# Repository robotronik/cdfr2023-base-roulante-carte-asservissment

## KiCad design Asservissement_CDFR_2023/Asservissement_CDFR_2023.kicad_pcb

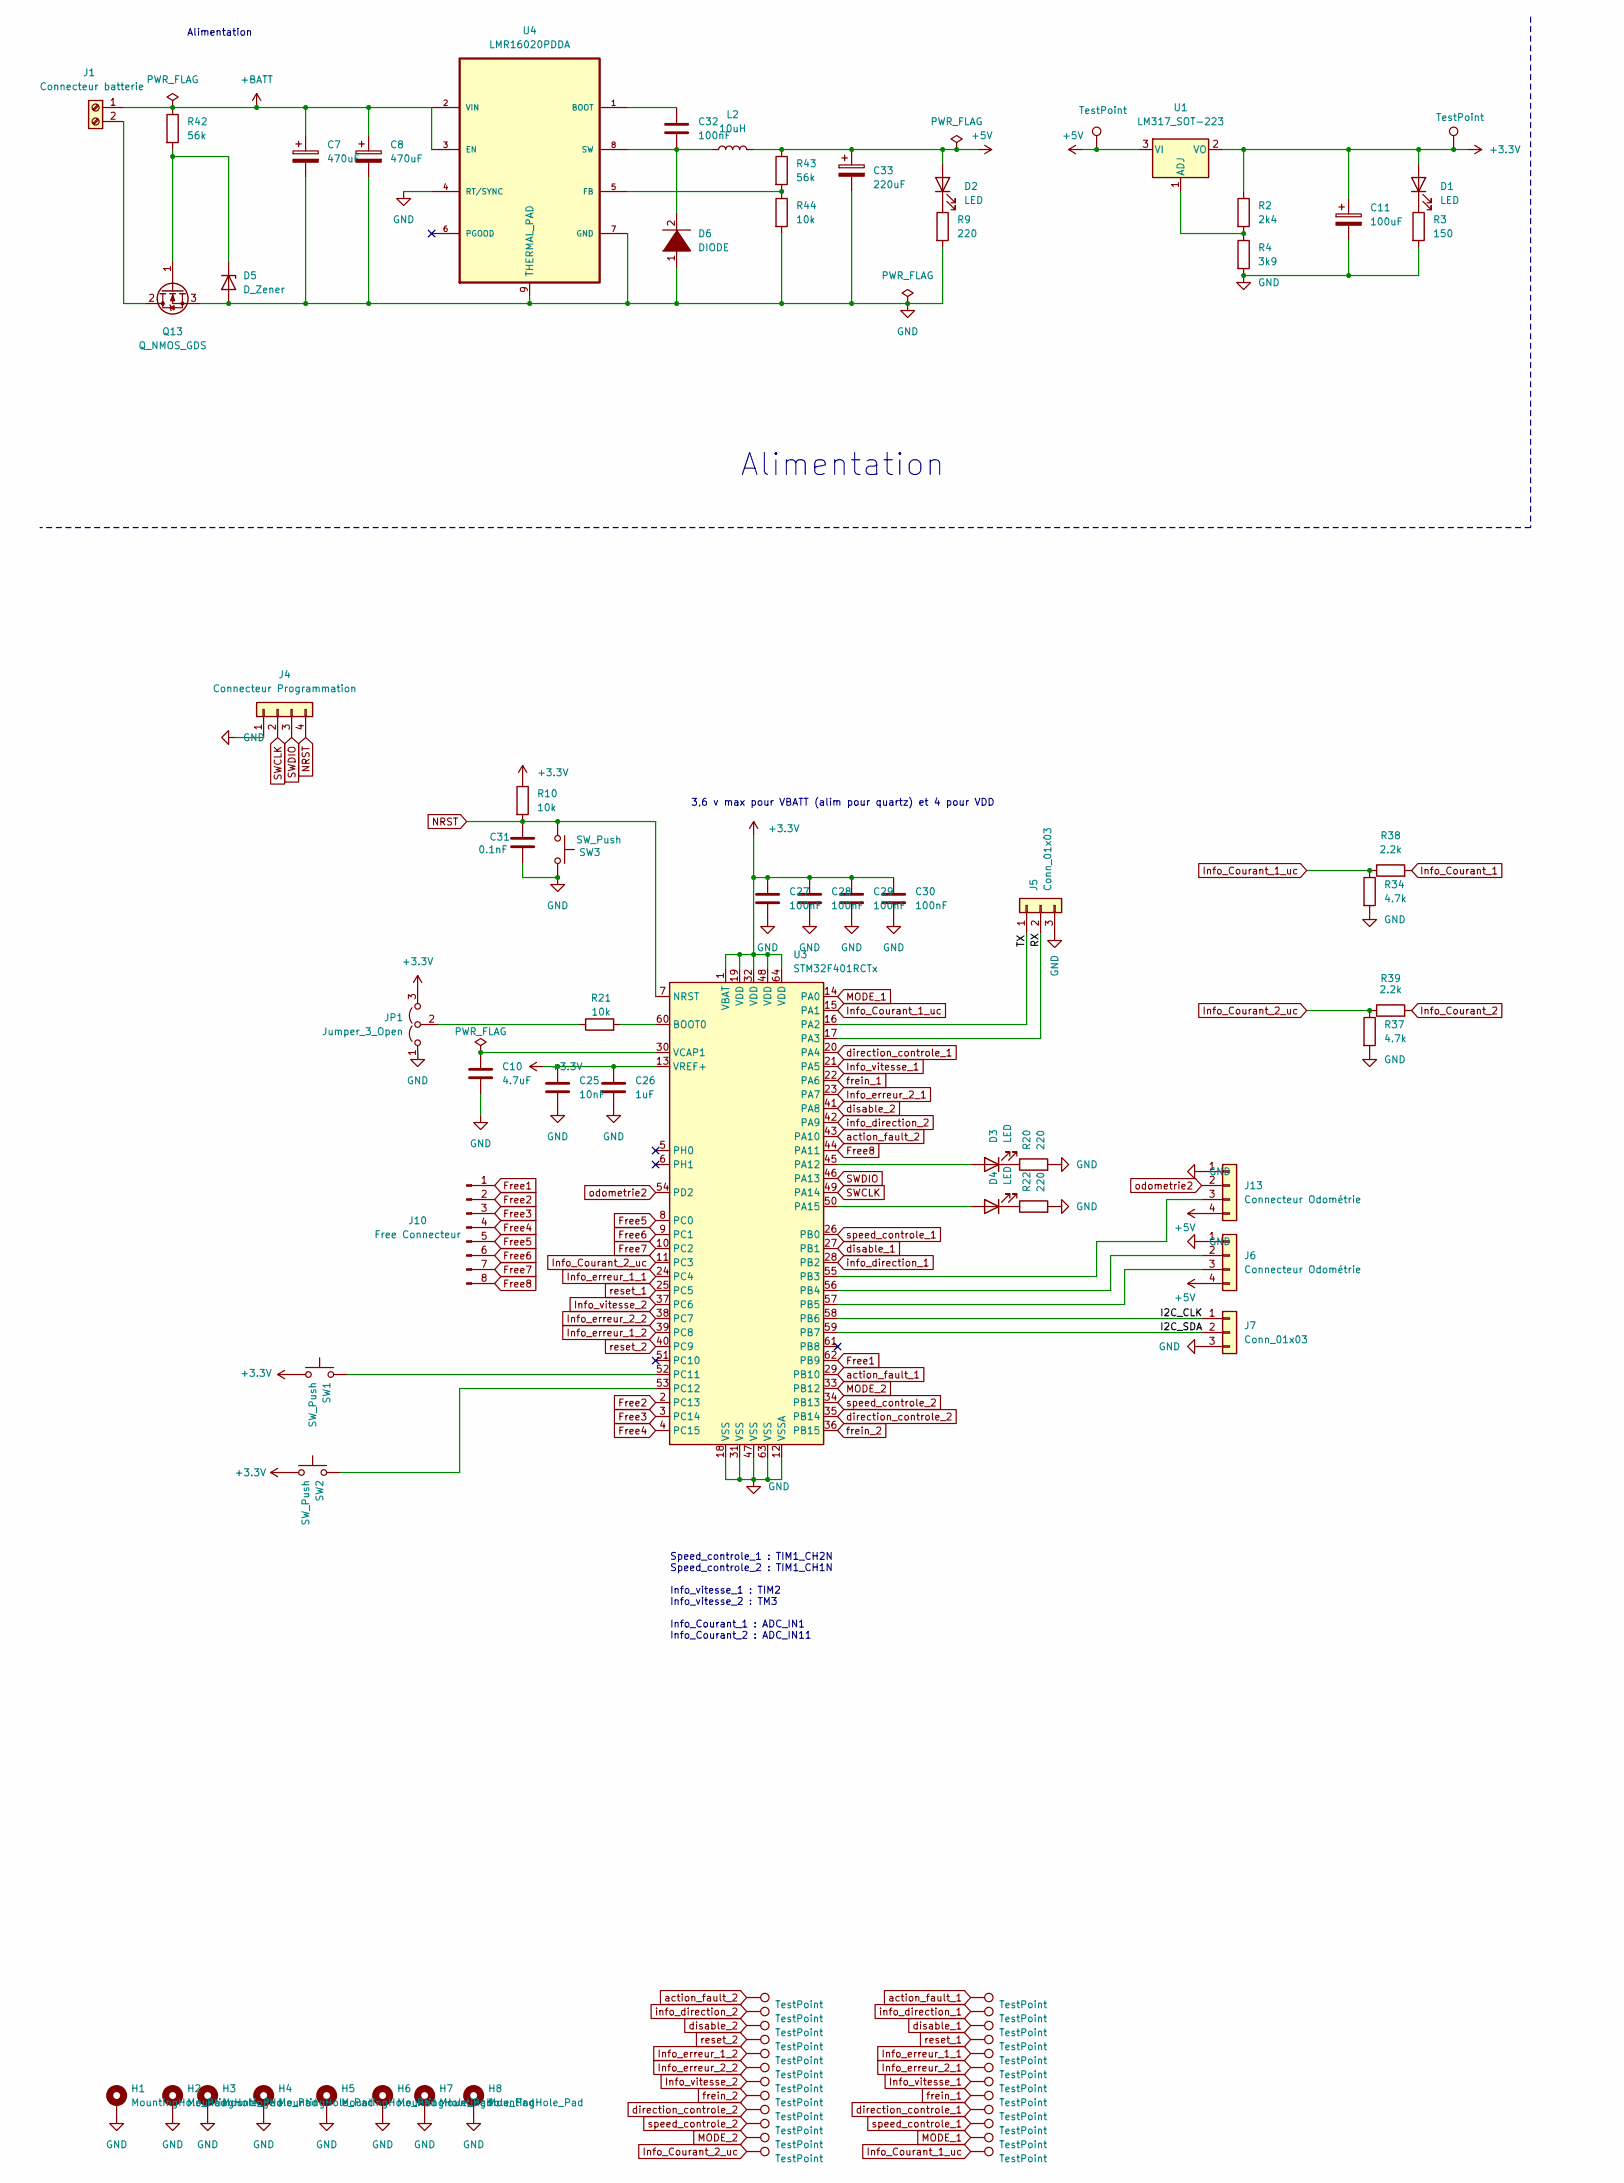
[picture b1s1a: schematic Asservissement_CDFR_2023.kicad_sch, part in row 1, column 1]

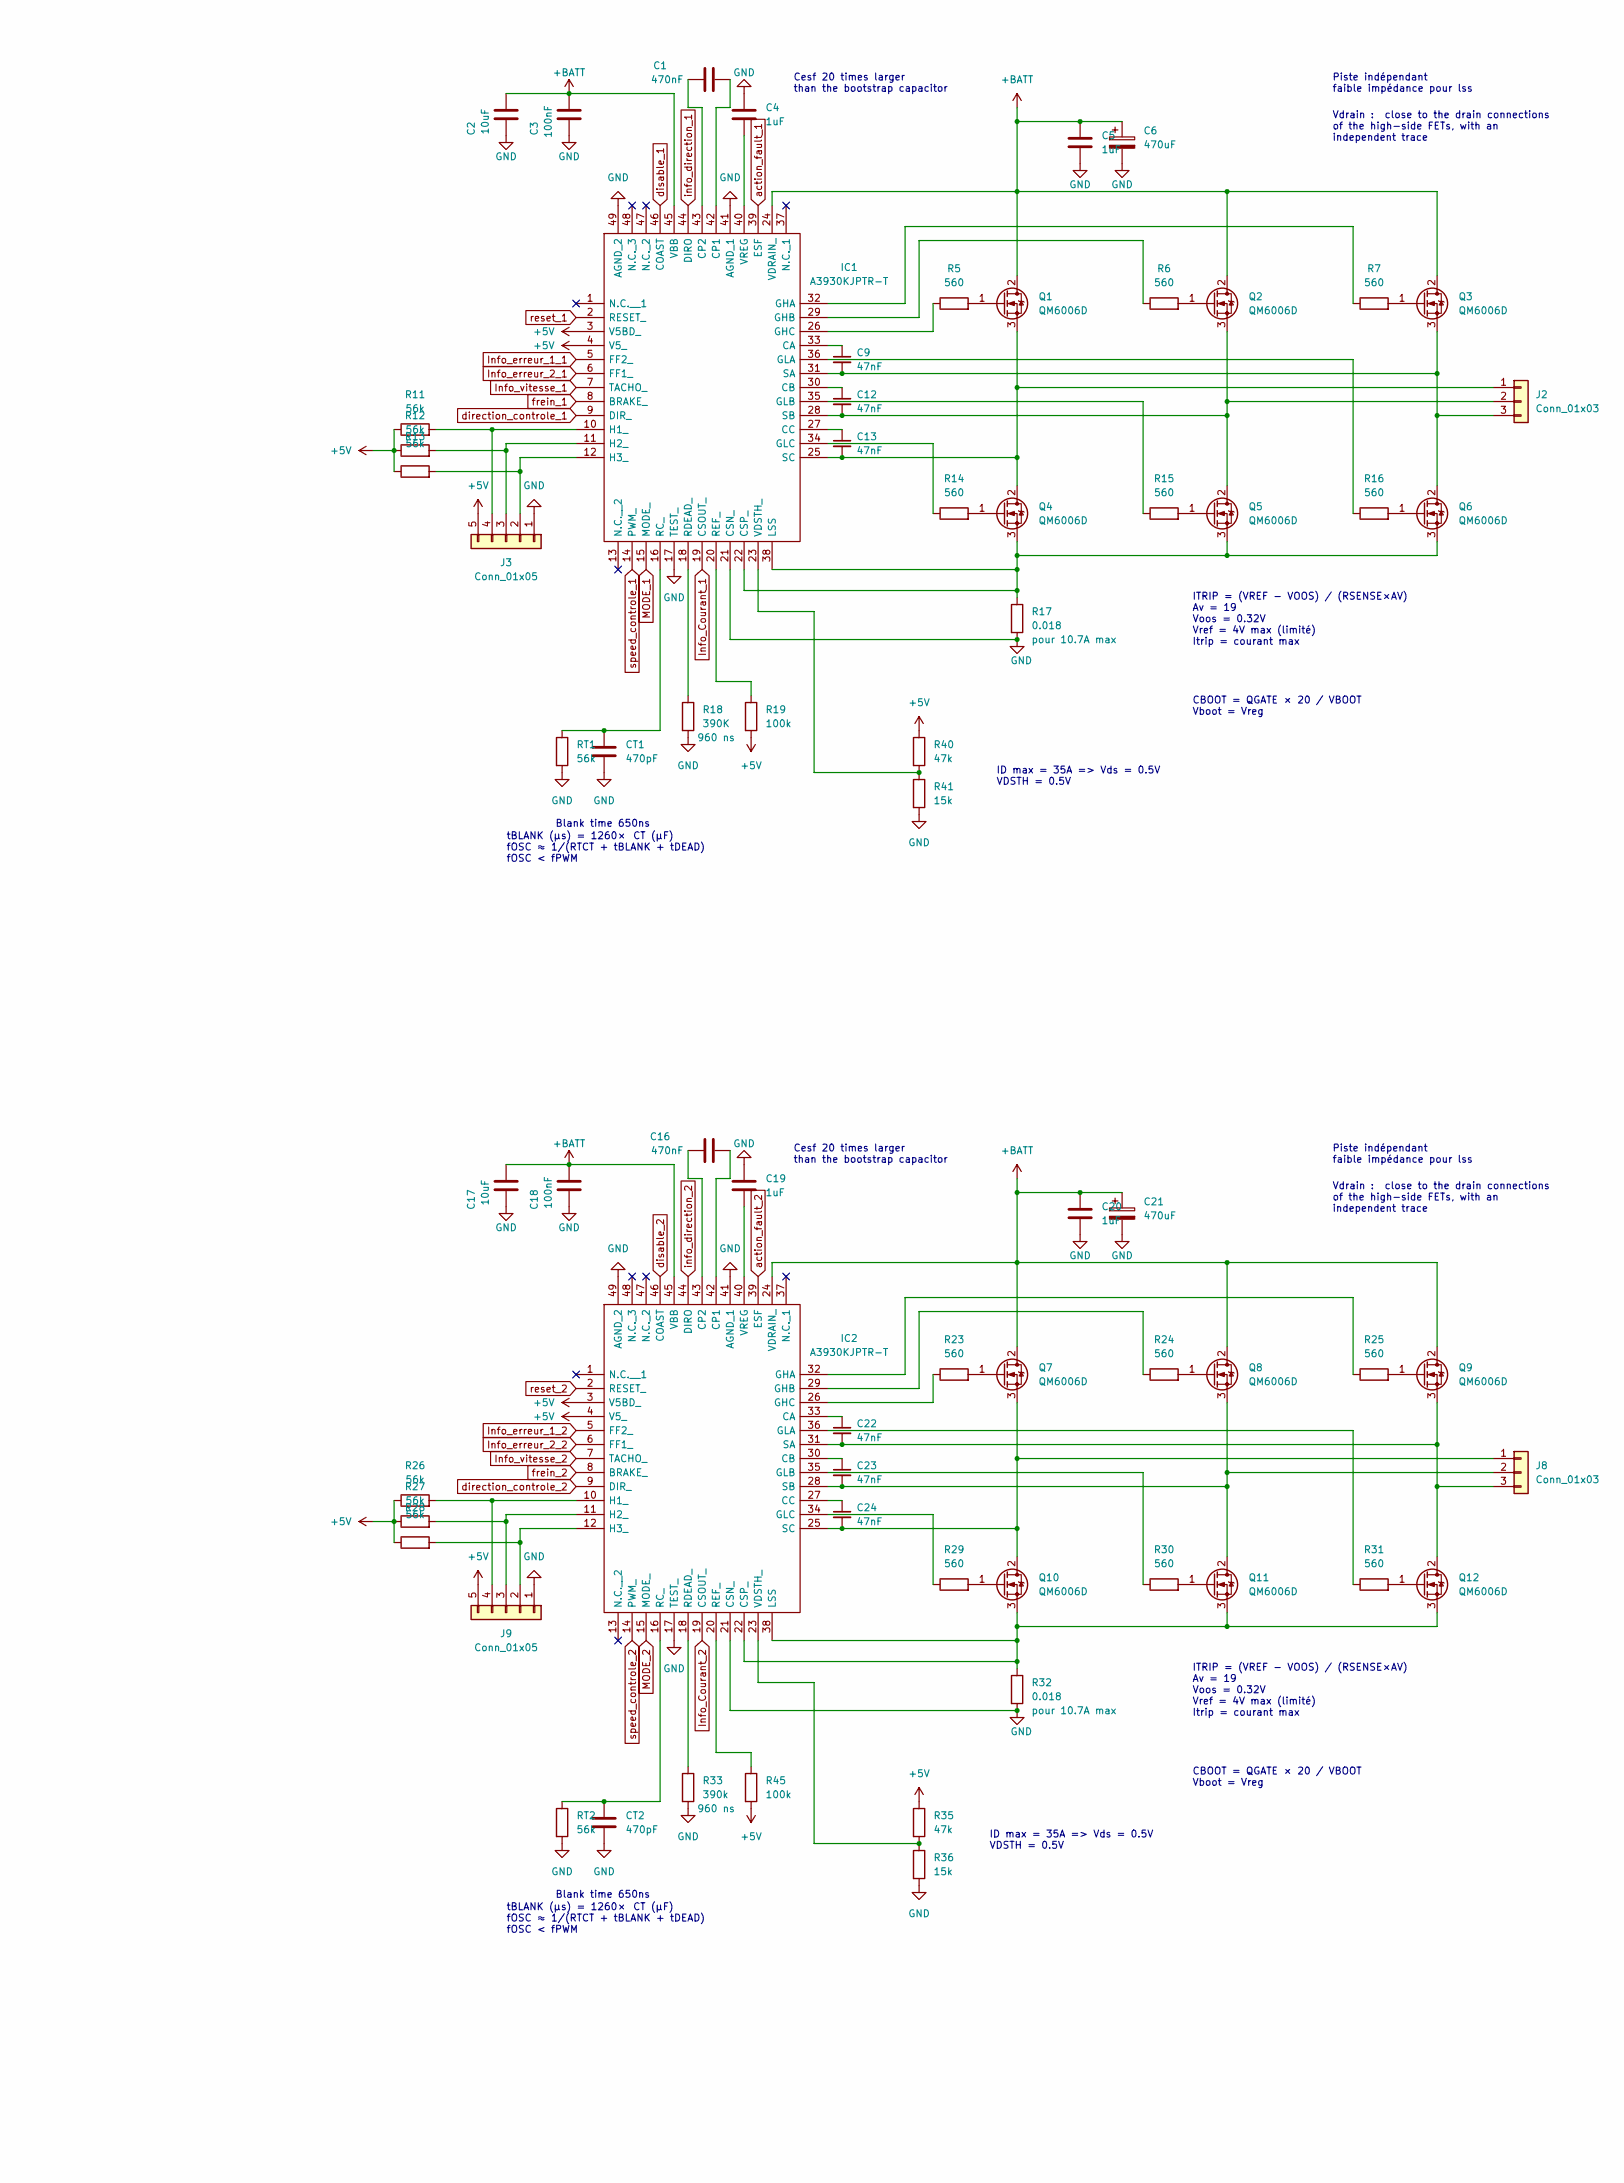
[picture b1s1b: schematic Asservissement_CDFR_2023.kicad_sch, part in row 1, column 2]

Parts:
C1, C16: 470nF; C_0805_2012Metric_Pad1.18x1.45mm_HandSolder
C2, C17: 10uF; C_0805_2012Metric_Pad1.18x1.45mm_HandSolder
C3, C18, C27, C28, C29, C30, C32: 100nF; C_0805_2012Metric_Pad1.18x1.45mm_HandSolder
C4, C5, C19, C20, C26: 1uF; C_0805_2012Metric_Pad1.18x1.45mm_HandSolder
C6, C7, C8, C21: 470uF; CP_Elec_10x10.5
C9, C12, C13, C22, C23, C24: 47nF; C_0805_2012Metric_Pad1.18x1.45mm_HandSolder
C10: 4.7uF; C_0805_2012Metric_Pad1.18x1.45mm_HandSolder
C11: 100uF; CP_Elec_10x10.5
C25: 10nF; C_0805_2012Metric_Pad1.18x1.45mm_HandSolder
C31: 0.1nF; C_0805_2012Metric_Pad1.18x1.45mm_HandSolder
C33: 220uF; CP_Elec_10x10.5
CT1, CT2: 470pF; C_0805_2012Metric_Pad1.18x1.45mm_HandSolder
D1, D2, D3, D4: LED; LED_0805_2012Metric_Pad1.15x1.40mm_HandSolder
D5: D_Zener; D_SOD-123
D6: DIODE; DIOM505270X240
H1, H2, H3, H4: MountingHole_Pad; MountingHole_3.2mm_M3_Pad_Via
H5, H6, H7, H8: MountingHole_Pad; MountingHole_2.7mm_Pad_Via
IC1, IC2: A3930KJPTR-T; A3930KJPTRT; Manufacturer_Part_Number A3930KJPTR-T
J1: Connecteur batterie; CUI_TBP01R1-508-02BE
J2, J8: Conn_01x03; CUI_TBP02R1-381-03BE
J3, J9: Conn_01x05; JST_XH_B5B-XH-A_1x05_P2.50mm_Vertical
J4: Connecteur Programmation; PinHeader_1x04_P2.54mm_Vertical
J5: Conn_01x03; PinHeader_1x03_P2.54mm_Vertical
J6, J13: Connecteur Odométrie; JST_XH_B4B-XH-A_1x04_P2.50mm_Vertical
J7: Conn_01x03; JST_XH_B3B-XH-A_1x03_P2.50mm_Vertical
J10: Free Connecteur; PinHeader_1x08_P2.54mm_Vertical
JP1: Jumper_3_Open; PinHeader_1x03_P2.54mm_Vertical
L2: 10uH; IND_IHLP_2525_CZ-M
Q1, Q2, Q3, Q4, Q5, Q6, Q7, Q8, Q9, Q10, Q11, Q12: QM6006D; TO-252-2
Q13: Q_NMOS_GDS; TO-252-2
R2: 2k4; R_0805_2012Metric_Pad1.20x1.40mm_HandSolder
R3: 150; R_0805_2012Metric_Pad1.20x1.40mm_HandSolder
R4: 3k9; R_0805_2012Metric_Pad1.20x1.40mm_HandSolder
R5, R6, R7, R14, R15, R16, R23, R24, R25, R29, R30, R31: 560; R_0805_2012Metric_Pad1.20x1.40mm_HandSolder
R9, R20, R22: 220; R_0805_2012Metric_Pad1.20x1.40mm_HandSolder
R10, R21, R44: 10k; R_0805_2012Metric_Pad1.20x1.40mm_HandSolder
R11, R12, R13, R26, R27, R28, R42, R43: 56k; R_0805_2012Metric_Pad1.20x1.40mm_HandSolder
R17, R32: 0.018; R_2512_6332Metric
R18: 390K; R_0805_2012Metric_Pad1.20x1.40mm_HandSolder
R19, R45: 100k; R_0805_2012Metric_Pad1.20x1.40mm_HandSolder
R33: 390k; R_0805_2012Metric_Pad1.20x1.40mm_HandSolder
R34, R37: 4.7k; R_0805_2012Metric_Pad1.20x1.40mm_HandSolder
R35, R40: 47k; R_0805_2012Metric_Pad1.20x1.40mm_HandSolder
R36, R41: 15k; R_0805_2012Metric_Pad1.20x1.40mm_HandSolder
R38, R39: 2.2k; R_0805_2012Metric_Pad1.20x1.40mm_HandSolder
RT1, RT2: 56k; R_0805_2012Metric_Pad1.20x1.40mm_HandSolder
SW1, SW2, SW3: SW_Push; SW_PUSH_6mm_H5mm
TP1, TP2, TP3, TP4, TP5, TP6, TP7, TP8, TP9, TP10, TP11, TP12, TP13, TP14, TP25, TP26, TP27, TP28, TP29, TP30, TP31, TP32, TP33, TP34, TP35, TP36: TestPoint; TestPoint_Pad_D1.0mm
U1: LM317_SOT-223; SOT-223-3_TabPin2
U3: STM32F401RCTx; LQFP-64_10x10mm_P0.5mm
U4: LMR16020PDDA; SOIC-8-1EP_3.9x4.9mm_P1.27mm_EP2.41x3.3mm

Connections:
+3.3V: C11.1, C25.1, C26.1, C27.1, C28.1, C29.1, C30.1, D1.2 (A), JP1.3 (B), R2.1, R10.1, SW1.1, SW2.1, TP14.1, U1.2 (VO), U3.1 (VBAT), U3.13 (VREF+), U3.19 (VDD), U3.32 (VDD), U3.48 (VDD), U3.64 (VDD)
+5V: C33.1, D2.2 (A), IC1.3 (V5BD_), IC1.4 (V5_), IC2.3 (V5BD_), IC2.4 (V5_), J3.5, J6.4, J9.5, J13.4, L2.2, R11.1, R12.1, R13.1, R19.2, R26.1, R27.1, R28.1, R35.1, R40.1, R43.1, R45.2, TP13.1, U1.3 (VI)
+BATT: C2.1, C3.1, C5.1, C6.1, C7.1, C8.1, C17.1, C18.1, C20.1, C21.1, IC1.24 (VDRAIN_), IC1.45 (VBB), IC2.24 (VDRAIN_), IC2.45 (VBB), J1.1, Q1.2 (D), Q2.2 (D), Q3.2 (D), Q7.2 (D), Q8.2 (D), Q9.2 (D), R42.1, U4.2 (VIN), U4.3 (EN)
/I2C_CLK: J7.1, U3.58 (PB6)
/I2C_SDA: J7.2, U3.59 (PB7)
/RX: J5.2, U3.17 (PA3)
/TX: J5.1, U3.16 (PA2)
Free1: J10.1, U3.62 (PB9)
Free2: J10.2, U3.2 (PC13)
Free3: J10.3, U3.3 (PC14)
Free4: J10.4, U3.4 (PC15)
Free5: J10.5, U3.8 (PC0)
Free6: J10.6, U3.9 (PC1)
Free7: J10.7, U3.10 (PC2)
Free8: J10.8, U3.44 (PA11)
GND: C2.2, C3.2, C4.1, C5.2, C6.2, C7.2, C8.2, C10.2, C11.2, C17.2, C18.2, C19.1, C20.2, C21.2, C25.2, C26.2, C27.2, C28.2, C29.2, C30.2, C31.2, C33.2, CT1.2, CT2.2, D5.2 (A), D6.1 (K), H1.1, H2.1, H3.1, H4.1, H5.1, H6.1, H7.1, H8.1, IC1.17 (TEST_), IC1.21 (CSN_), IC1.41 (AGND_1), IC1.49 (AGND_2), IC2.17 (TEST_), IC2.21 (CSN_), IC2.41 (AGND_1), IC2.49 (AGND_2), J3.1, J4.1, J5.3, J6.1, J7.3, J9.1, J13.1, JP1.1 (A), Q13.3 (S), R3.2, R4.2, R9.2, R17.2, R18.2, R20.2, R22.2, R32.2, R33.2, R34.2, R36.2, R37.2, R41.2, R44.2, RT1.2, RT2.2, SW3.2, U3.12 (VSSA), U3.18 (VSS), U3.31 (VSS), U3.47 (VSS), U3.63 (VSS), U4.4 (RT/SYNC), U4.7 (GND), U4.9 (THERMAL_PAD)
Info_Courant_1: IC1.19 (CSOUT_), R38.2
Info_Courant_1_uc: R34.1, R38.1, TP36.1, U3.15 (PA1)
Info_Courant_2: IC2.19 (CSOUT_), R39.2
Info_Courant_2_uc: R37.1, R39.1, TP1.1, U3.11 (PC3)
Info_erreur_1_1: IC1.5 (FF2_), TP29.1, U3.24 (PC4)
Info_erreur_1_2: IC2.5 (FF2_), TP11.1, U3.39 (PC8)
Info_erreur_2_1: IC1.6 (FF1_), TP30.1, U3.23 (PA7)
Info_erreur_2_2: IC2.6 (FF1_), TP12.1, U3.38 (PC7)
Info_vitesse_1: IC1.7 (TACHO_), TP31.1, U3.21 (PA5)
Info_vitesse_2: IC2.7 (TACHO_), TP5.1, U3.37 (PC6)
MODE_1: IC1.15 (MODE_), TP35.1, U3.14 (PA0)
MODE_2: IC2.15 (MODE_), TP2.1, U3.33 (PB12)
NRST: C31.1, J4.4, R10.2, SW3.1, U3.7 (NRST)
unnamed: D1.1 (K), R3.1
unnamed: D2.1 (K), R9.1
unnamed: D3.2 (A), U3.45 (PA12)
unnamed: D3.1 (K), R20.1
unnamed: D4.2 (A), U3.50 (PA15)
unnamed: D4.1 (K), R22.1
unnamed: D5.1 (K), Q13.1 (G), R42.2
unnamed: C32.2, D6.2 (A), L2.1, U4.8 (SW)
unnamed: C9.1, IC1.33 (CA)
unnamed: C12.1, IC1.30 (CB)
unnamed: C13.1, IC1.27 (CC)
unnamed: C1.2, IC1.42 (CP1)
unnamed: C1.1, IC1.43 (CP2)
unnamed: IC1.22 (CSP_), IC1.38 (LSS), Q4.3 (S), Q5.3 (S), Q6.3 (S), R17.1
unnamed: IC1.32 (GHA), R7.1
unnamed: IC1.29 (GHB), R6.1
unnamed: IC1.26 (GHC), R5.1
unnamed: IC1.36 (GLA), R16.1
unnamed: IC1.35 (GLB), R15.1
unnamed: IC1.34 (GLC), R14.1
unnamed: IC1.10 (H1_), J3.4, R11.2
unnamed: IC1.11 (H2_), J3.3, R12.2
unnamed: IC1.12 (H3_), J3.2, R13.2
unnamed: CT1.1, IC1.16 (RC_), RT1.1
unnamed: IC1.18 (RDEAD_), R18.1
unnamed: IC1.20 (REF_), R19.1
unnamed: C9.2, IC1.31 (SA), J2.3, Q3.3 (S), Q6.2 (D)
unnamed: C12.2, IC1.28 (SB), J2.2, Q2.3 (S), Q5.2 (D)
unnamed: C13.2, IC1.25 (SC), J2.1, Q1.3 (S), Q4.2 (D)
unnamed: IC1.23 (VDSTH_), R40.2, R41.1
unnamed: C4.2, IC1.40 (VREG)
unnamed: C22.1, IC2.33 (CA)
unnamed: C23.1, IC2.30 (CB)
unnamed: C24.1, IC2.27 (CC)
unnamed: C16.2, IC2.42 (CP1)
unnamed: C16.1, IC2.43 (CP2)
unnamed: IC2.22 (CSP_), IC2.38 (LSS), Q10.3 (S), Q11.3 (S), Q12.3 (S), R32.1
unnamed: IC2.32 (GHA), R25.1
unnamed: IC2.29 (GHB), R24.1
unnamed: IC2.26 (GHC), R23.1
unnamed: IC2.36 (GLA), R31.1
unnamed: IC2.35 (GLB), R30.1
unnamed: IC2.34 (GLC), R29.1
unnamed: IC2.10 (H1_), J9.4, R26.2
unnamed: IC2.11 (H2_), J9.3, R27.2
unnamed: IC2.12 (H3_), J9.2, R28.2
unnamed: CT2.1, IC2.16 (RC_), RT2.1
unnamed: IC2.18 (RDEAD_), R33.1
unnamed: IC2.20 (REF_), R45.1
unnamed: C22.2, IC2.31 (SA), J8.3, Q9.3 (S), Q12.2 (D)
unnamed: C23.2, IC2.28 (SB), J8.2, Q8.3 (S), Q11.2 (D)
unnamed: C24.2, IC2.25 (SC), J8.1, Q7.3 (S), Q10.2 (D)
unnamed: IC2.23 (VDSTH_), R35.2, R36.1
unnamed: C19.2, IC2.40 (VREG)
unnamed: J1.2, Q13.2 (D)
unnamed: J6.2, U3.56 (PB4)
unnamed: J6.3, U3.57 (PB5)
unnamed: J13.3, U3.55 (PB3)
unnamed: JP1.2 (C), R21.1
unnamed: Q1.1 (G), R5.2
unnamed: Q2.1 (G), R6.2
unnamed: Q3.1 (G), R7.2
unnamed: Q4.1 (G), R14.2
unnamed: Q5.1 (G), R15.2
unnamed: Q6.1 (G), R16.2
unnamed: Q7.1 (G), R23.2
unnamed: Q8.1 (G), R24.2
unnamed: Q9.1 (G), R25.2
unnamed: Q10.1 (G), R29.2
unnamed: Q11.1 (G), R30.2
unnamed: Q12.1 (G), R31.2
unnamed: R2.2, R4.1, U1.1 (ADJ)
unnamed: R21.2, U3.60 (BOOT0)
unnamed: SW1.2, U3.52 (PC11)
unnamed: SW2.2, U3.53 (PC12)
unnamed: C10.1, U3.30 (VCAP1)
unnamed: C32.1, U4.1 (BOOT)
unnamed: R43.2, R44.1, U4.5 (FB)
SWCLK: J4.2, U3.49 (PA14)
SWDIO: J4.3, U3.46 (PA13)
action_fault_1: IC1.39 (ESF), TP25.1, U3.29 (PB10)
action_fault_2: IC2.39 (ESF), TP7.1, U3.43 (PA10)
direction_controle_1: IC1.9 (DIR_), TP33.1, U3.20 (PA4)
direction_controle_2: IC2.9 (DIR_), TP3.1, U3.35 (PB14)
disable_1: IC1.46 (COAST), TP27.1, U3.27 (PB1)
disable_2: IC2.46 (COAST), TP9.1, U3.41 (PA8)
frein_1: IC1.8 (BRAKE_), TP32.1, U3.22 (PA6)
frein_2: IC2.8 (BRAKE_), TP6.1, U3.36 (PB15)
info_direction_1: IC1.44 (DIRO), TP26.1, U3.28 (PB2)
info_direction_2: IC2.44 (DIRO), TP8.1, U3.42 (PA9)
odometrie2: J13.2, U3.54 (PD2)
reset_1: IC1.2 (RESET_), TP28.1, U3.25 (PC5)
reset_2: IC2.2 (RESET_), TP10.1, U3.40 (PC9)
speed_controle_1: IC1.14 (PWM_), TP34.1, U3.26 (PB0)
speed_controle_2: IC2.14 (PWM_), TP4.1, U3.34 (PB13)

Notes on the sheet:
tBLANK (µs) = 1260× CT (µF) fOSC ≈ 1/(RTCT + tBLANK + tDEAD) fOSC < fPWM
Blank time 650ns
Alimentation
ITRIP = (VREF - VOOS) / (RSENSE×AV) Av = 19 Voos = 0.32V Vref = 4V max (limité) Itrip = courant max
CBOOT = QGATE × 20 / VBOOT Vboot = Vreg
Speed_controle_1 : TIM1_CH2N Speed_controle_2 : TIM1_CH1N Info_vitesse_1 : TIM2 Info_vitesse_2 : TM3 Info_Courant_1 : ADC_IN1 Info_Courant_2 : ADC_IN11
ID max = 35A => Vds = 0.5V VDSTH = 0.5V
Vdrain : close to the drain connections of the high-side FETs, with an independent trace
Piste indépendant faible impédance pour lss
Cesf 20 times larger than the bootstrap capacitor
3,6 v max pour VBATT (alim pour quartz) et 4 pour VDD

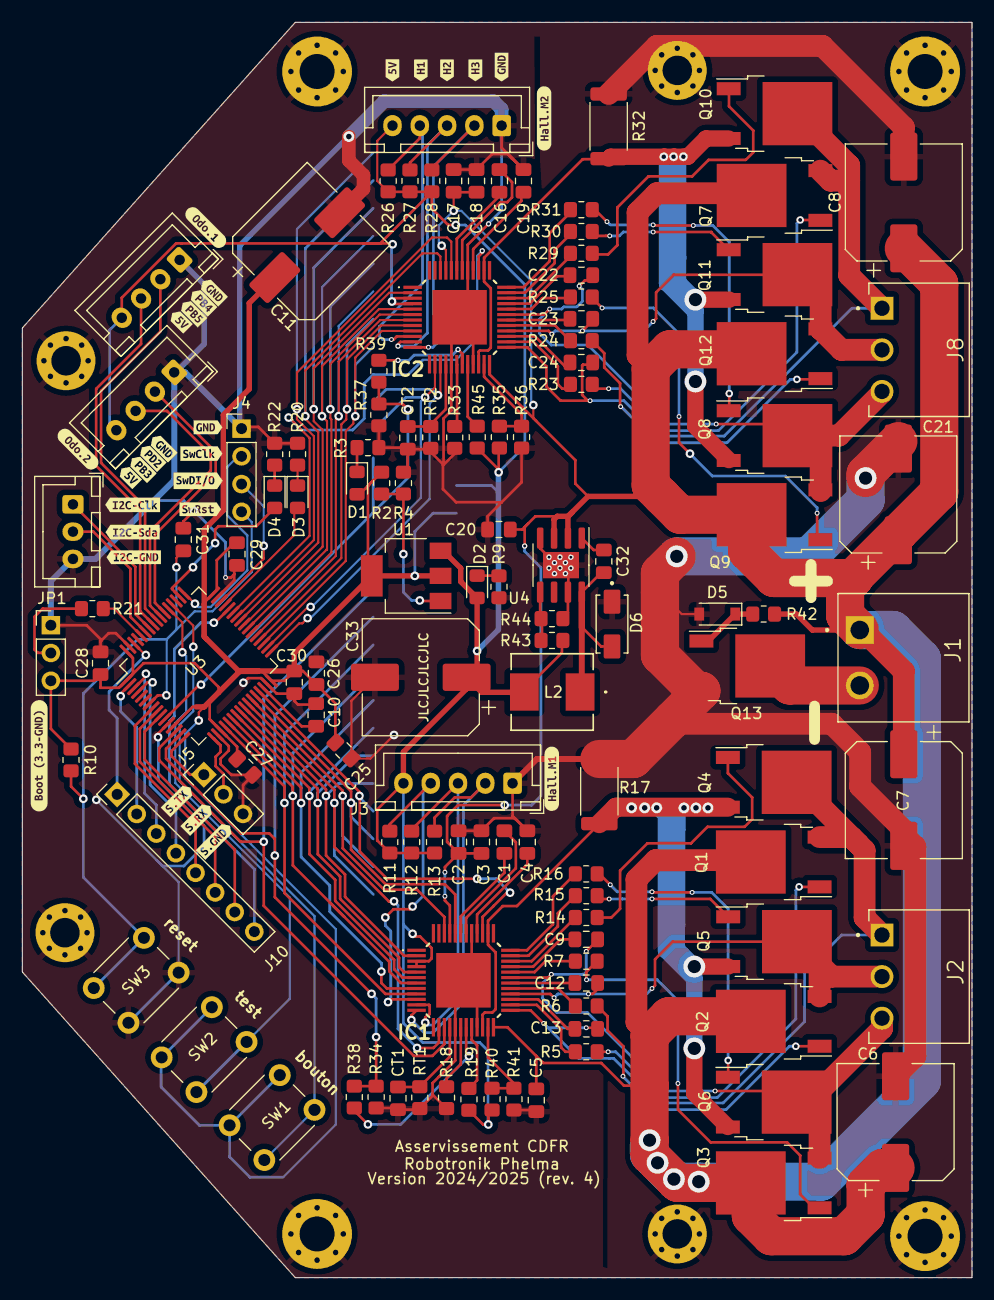
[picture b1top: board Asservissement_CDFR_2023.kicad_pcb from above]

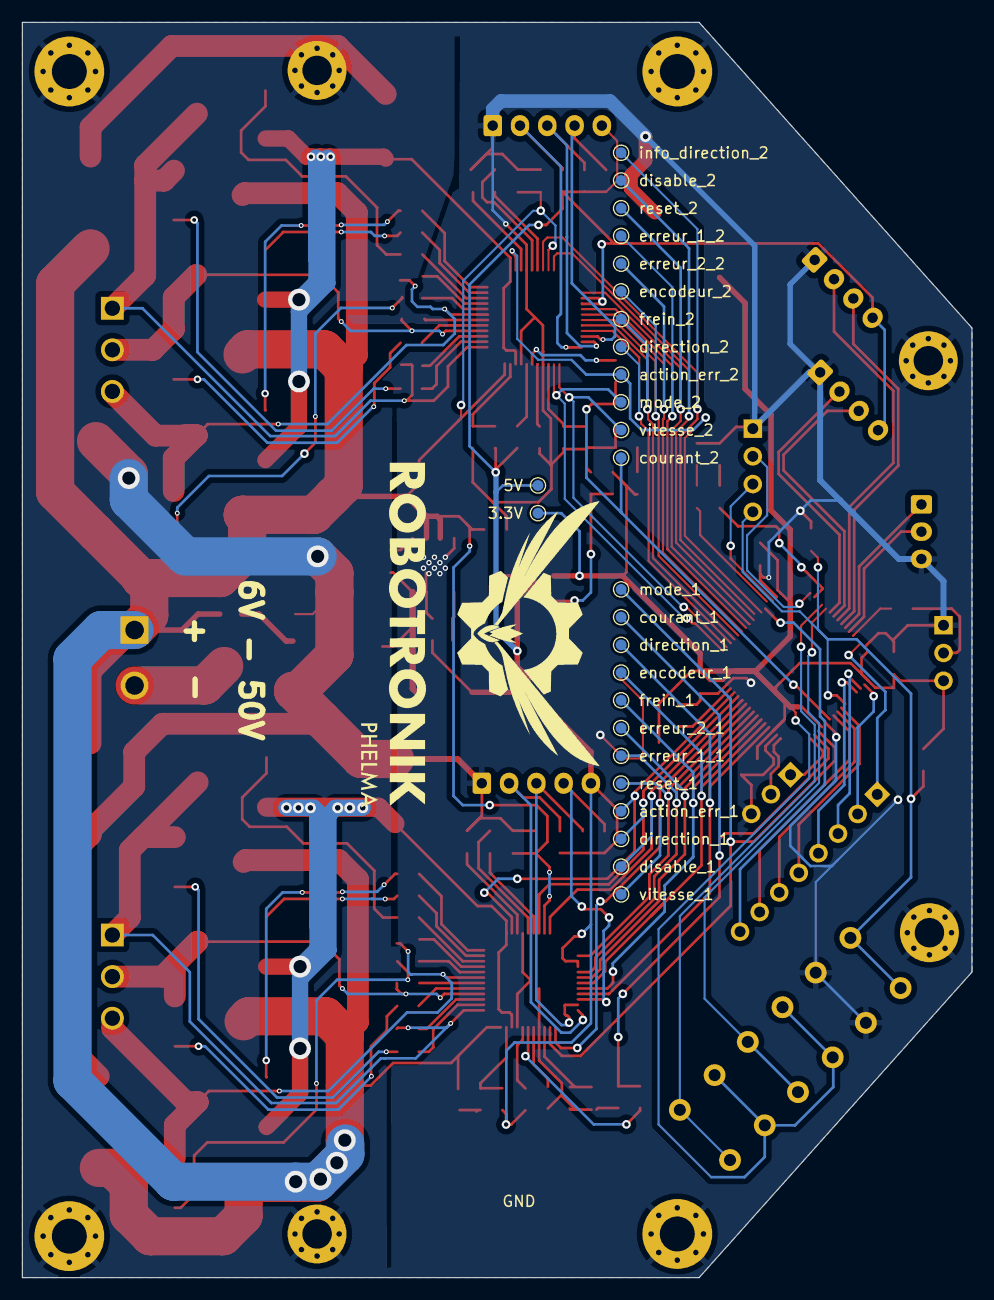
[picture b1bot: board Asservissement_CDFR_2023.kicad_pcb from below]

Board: 2 copper layers, 87.0 x 115.0 mm, 180 parts (26 on the bottom side), 124 nets.

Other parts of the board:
kibuzzard-637D41F7: G***; kibuzzard-637D41F7
kibuzzard-637D42B7: G***; kibuzzard-637D42B7
kibuzzard-637D42C2: G***; kibuzzard-637D42C2
kibuzzard-637D42CB: G***; kibuzzard-637D42CB
kibuzzard-637D42F0: G***; kibuzzard-637D42F0
kibuzzard-637D43BC: G***; kibuzzard-637D43BC
kibuzzard-637D43CD: G***; kibuzzard-637D43CD
kibuzzard-637D44C4: G***; kibuzzard-637D44C4
kibuzzard-637D44E0: G***; kibuzzard-637D44E0
kibuzzard-637D45A0: G***; kibuzzard-637D45A0
kibuzzard-637D428D: G***; kibuzzard-637D428D
kibuzzard-637D436E: G***; kibuzzard-637D436E
kibuzzard-637D437D: G***; kibuzzard-637D437D
kibuzzard-637D438C: G***; kibuzzard-637D438C
kibuzzard-637D4204: G***; kibuzzard-637D4204
kibuzzard-637D4217: G***; kibuzzard-637D4217
kibuzzard-637D4301: G***; kibuzzard-637D4301
kibuzzard-637D4322: G***; kibuzzard-637D4322
kibuzzard-637D4331: G***; kibuzzard-637D4331
kibuzzard-637D4374: G***; kibuzzard-637D4374
kibuzzard-637D4386: G***; kibuzzard-637D4386
kibuzzard-637D4446, kibuzzard-637D4446#2: G***; kibuzzard-637D4446
kibuzzard-637D4455: G***; kibuzzard-637D4455
kibuzzard-637D4463, kibuzzard-637D4463#2: G***; kibuzzard-637D4463
kibuzzard-637D4536: G***; kibuzzard-637D4536
kibuzzard-eD: G***; kibuzzard-637D447D

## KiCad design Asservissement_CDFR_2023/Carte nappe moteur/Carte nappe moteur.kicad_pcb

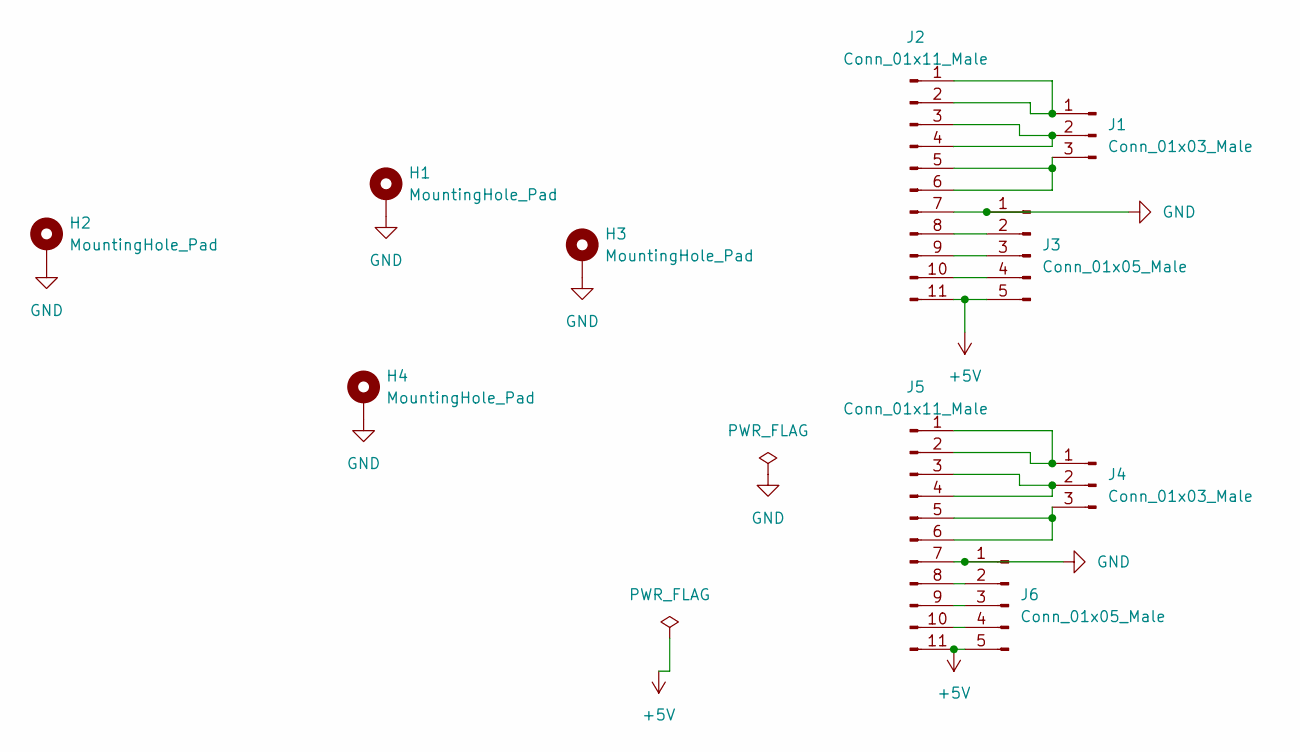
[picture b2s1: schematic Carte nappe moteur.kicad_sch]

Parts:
H1, H2, H3, H4: MountingHole_Pad; MountingHole_3.2mm_M3_Pad_Via
J1, J4: Conn_01x03_Male; CUI_TBP02R1-381-03BE
J2, J5: Conn_01x11_Male; Molex-52610-1133
J3, J6: Conn_01x05_Male; CUI_TBP02R1-381-05BE

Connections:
+5V: J2.11, J3.5, J5.11, J6.5
GND: H1.1, H2.1, H3.1, H4.1, J2.7, J3.1, J5.7, J6.1; also elsewhere on the board
unnamed: J1.1, J2.1, J2.2
unnamed: J1.2, J2.3, J2.4
unnamed: J1.3, J2.5, J2.6
unnamed: J2.8, J3.2
unnamed: J2.9, J3.3
unnamed: J2.10, J3.4
unnamed: J4.1, J5.1, J5.2
unnamed: J4.2, J5.3, J5.4
unnamed: J4.3, J5.5, J5.6
unnamed: J5.8, J6.2
unnamed: J5.9, J6.3
unnamed: J5.10, J6.4

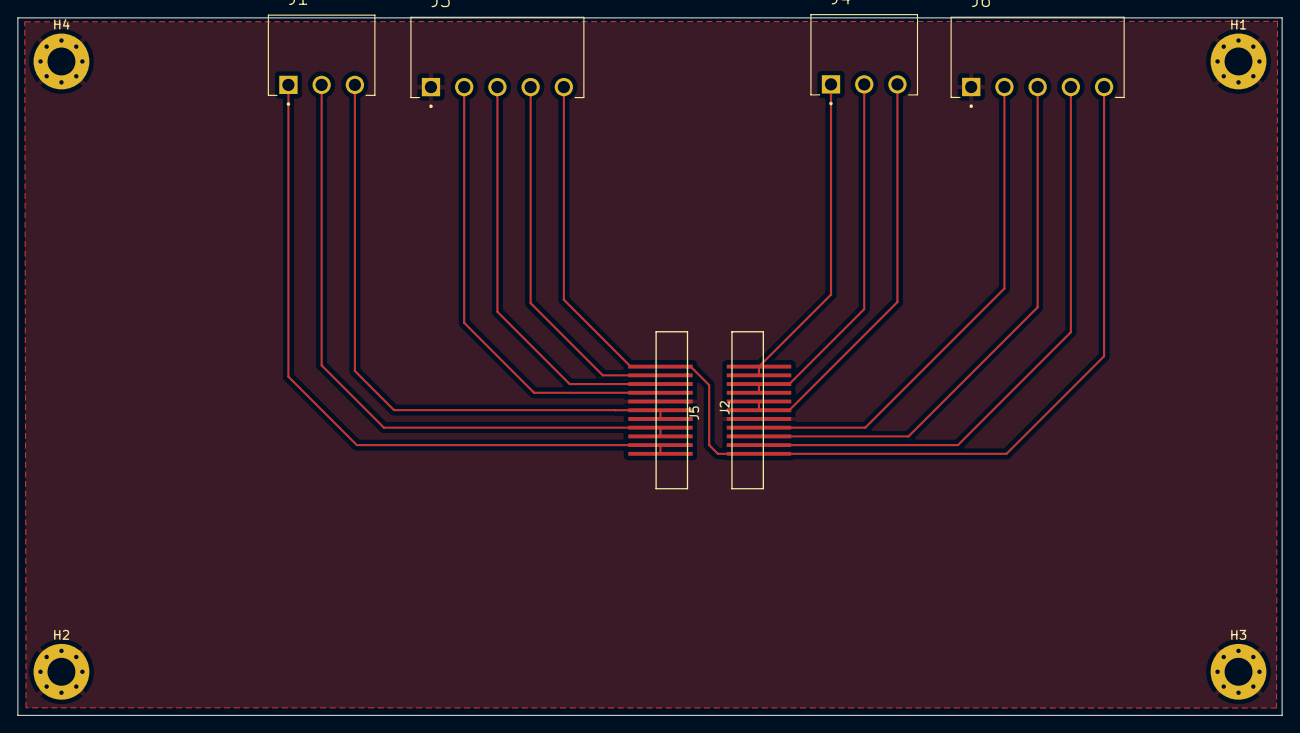
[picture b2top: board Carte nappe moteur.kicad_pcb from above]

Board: 2 copper layers, 145.0 x 80.0 mm, 10 parts (0 on the bottom side), 14 nets.

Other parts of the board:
H?: MountingHole_Pad; MountingHole_3.2mm_M3_Pad_Via

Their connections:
GND: H?.1; also elsewhere on the board

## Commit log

2022-11-12 add one driver a3930
2022-11-13 Add files via upload
    Copie pour deuxième moteur
2022-11-16 driver set up
2022-11-17 Maj de l'alimenter ok reste microcontrol
2022-11-18 Added gitignore for backups
2022-11-18 Buck converter, fix gitignore
2022-11-18 NMOS reverse voltage protection
2022-11-18 wtf why doesn't the gitignore update
2022-11-19 schematic finished
2022-11-21 Pré-routage carte asservissement (en attente de correctif sur l'ordre des pins du stm32)
2022-11-21 uController modification pinout
2022-11-21 capacitor error
2022-11-22 Routing almost done
2022-11-24 Add files via upload
    Rounded corners
2022-11-24 Fix Boost converter
2022-11-26 New buck routing + caps removal + fix ground on thermal pad for LMR16020 + removal of curved broder
2022-12-15 Carte pour nappe moteur 1.0
2023-01-30 chagement schemas
2023-01-30 chagement composant
2023-01-31 routing updated to match new capacitors
2023-02-14 add resistor for the crystal, add capacitor to Vcap, add logo and text for the voltage tolerance
2023-02-14 add name and version
2023-02-15 add jlcjlcjlc
2023-03-19 change one resistor
2025-02-03 V4 add button, test point, remove quartz, pot and fix current
2025-02-03 commande v4
2025-05-14 update ibom
